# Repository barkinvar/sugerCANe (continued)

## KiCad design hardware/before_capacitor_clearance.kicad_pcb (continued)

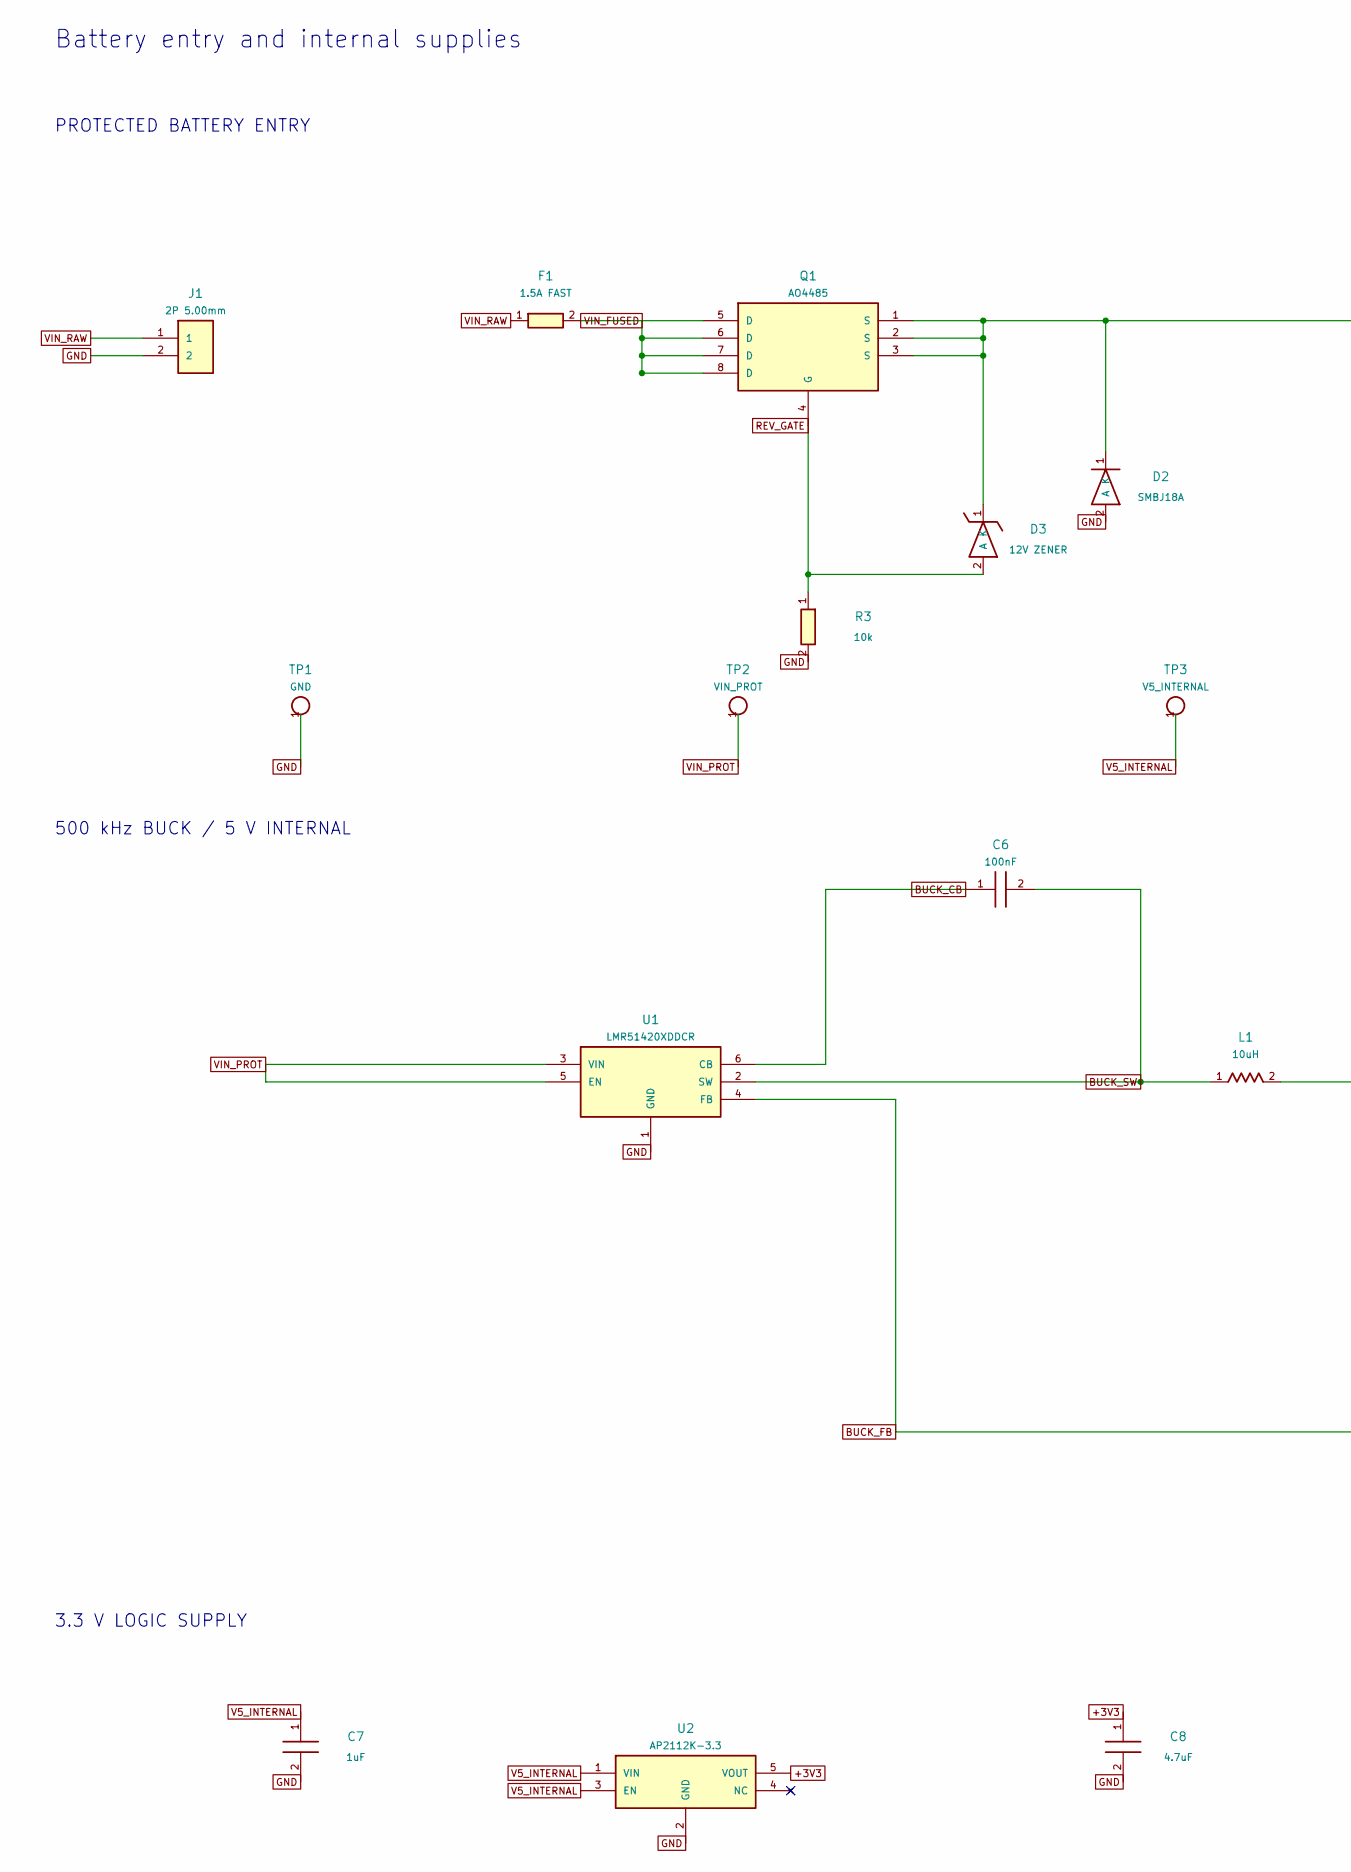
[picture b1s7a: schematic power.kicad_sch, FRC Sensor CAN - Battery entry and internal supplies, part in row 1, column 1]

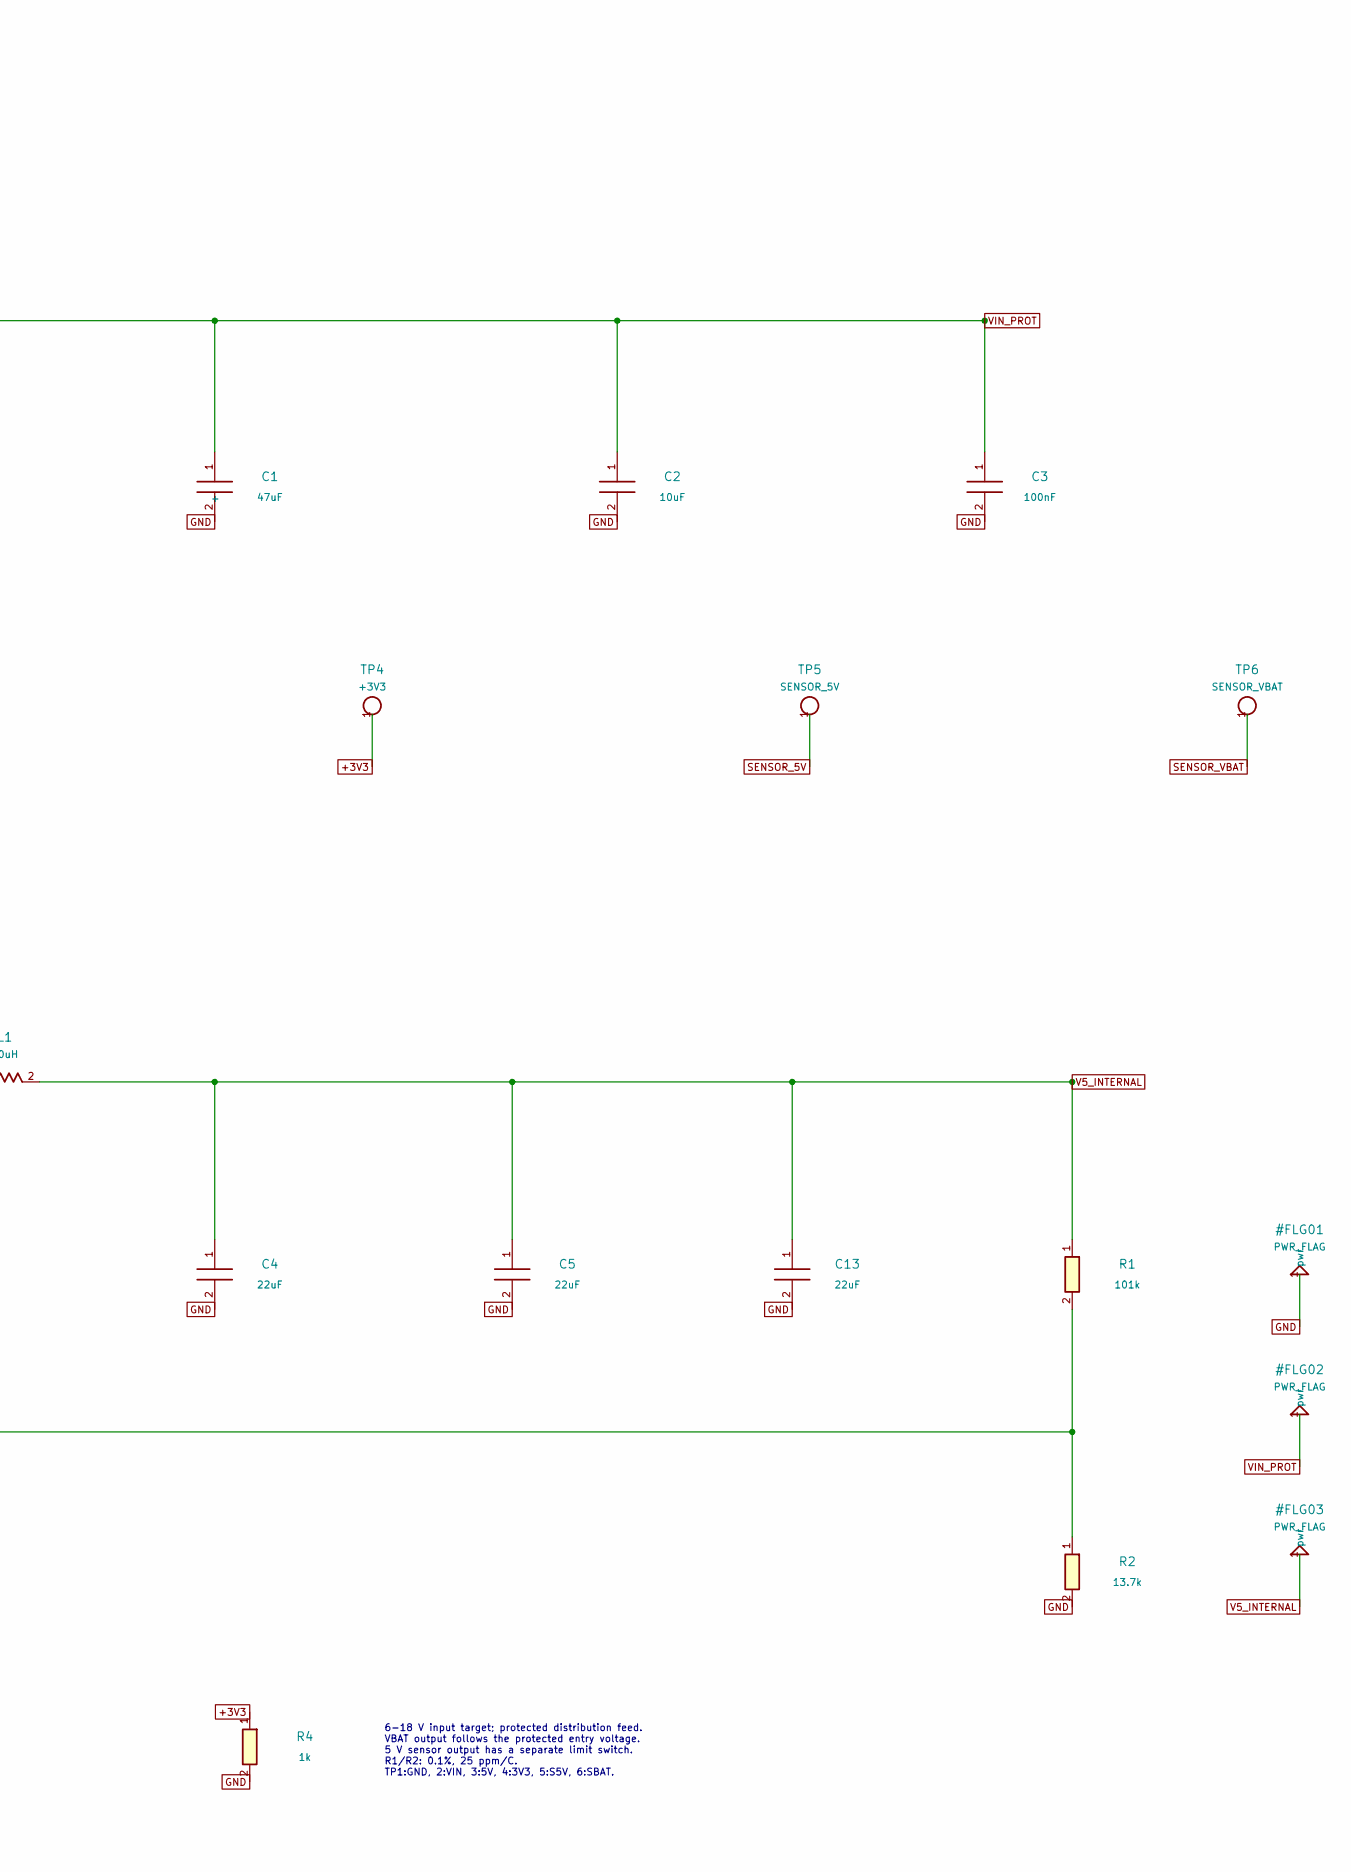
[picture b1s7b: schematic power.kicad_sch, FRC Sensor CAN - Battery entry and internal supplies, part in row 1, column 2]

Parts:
C1: 47uF; CP_Elec_6.3x5.8; MPN EEE-FK1V470P
C2: 10uF; C_1210_3225Metric; MPN CL32B106KBJNNWE
C3, C6: 100nF; C_0805_2012Metric; MPN CC0805KRX7R9BB104
C4, C5, C13: 22uF; C_1206_3216Metric; MPN CL31A226KAHNNNE
C7: 1uF; C_0805_2012Metric; MPN CC0805KKX7R9BB105
C8: 4.7uF; C_0805_2012Metric; MPN TMK212AB7475KG-T
D2: SMBJ18A; D_SMB; MPN SMBJ18A-E3/52
D3: 12V ZENER; D_SOD-123; MPN MMSZ12T1G
F1: 1.5A FAST; Fuse_Littelfuse-NANO2-451_453; MPN 045101.5MRL
J1: 2P 5.00mm; Wuerth_691137710002; MPN 691137710002
L1: 10uH; L_Bourns_SRP7028A_7.3x6.6mm; MPN SRP7028A-100M
Q1: AO4485; SOIC-8_3.9x4.9mm_P1.27mm; MPN AO4485
R1: 101k; R_0805_2012Metric; MPN RT0805BRD07101KL
R2: 13.7k; R_0805_2012Metric; MPN RT0805BRD0713K7L
R3: 10k; R_0805_2012Metric; MPN RC0805FR-0710KL
R4: 1k; R_0805_2012Metric; MPN RC0805FR-071KL
TP1: GND; TestPoint_Pad_D2.0mm
TP2: VIN_PROT; TestPoint_Pad_D2.0mm
TP3: V5_INTERNAL; TestPoint_Pad_D2.0mm
TP4: +3V3; TestPoint_Pad_D2.0mm
TP5: SENSOR_5V; TestPoint_Pad_D2.0mm
TP6: SENSOR_VBAT; TestPoint_Pad_D2.0mm
U1: LMR51420XDDCR; TSOT-23-6; MPN LMR51420XDDCR
U2: AP2112K-3.3; SOT-23-5; MPN AP2112K-3.3TRG1

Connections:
+3V3: C8.1, R4.1, TP4.1, U2.5 (VOUT); also elsewhere on the board
BUCK_CB: C6.1, U1.6 (CB)
BUCK_FB: R1.2, R2.1, U1.4 (FB)
BUCK_SW: C6.2, L1.1, U1.2 (SW)
GND: C1.2, C2.2, C3.2, C4.2, C5.2, C7.2, C8.2, C13.2, D2.2 (A), J1.2, R2.2, R3.2, R4.2, TP1.1, U1.1 (GND), U2.2 (GND); also elsewhere on the board
REV_GATE: D3.2 (A), Q1.4 (G), R3.1
SENSOR_5V: TP5.1; also elsewhere on the board
SENSOR_VBAT: TP6.1; also elsewhere on the board
V5_INTERNAL: C4.1, C5.1, C7.1, C13.1, L1.2, R1.1, TP3.1, U2.1 (VIN), U2.3 (EN); also elsewhere on the board
VIN_FUSED: F1.2, Q1.5 (D), Q1.6 (D), Q1.7 (D), Q1.8 (D)
VIN_PROT: C1.1 (+), C2.1, C3.1, D2.1 (K), D3.1 (K), Q1.1 (S), Q1.2 (S), Q1.3 (S), TP2.1, U1.3 (VIN), U1.5 (EN); also elsewhere on the board
VIN_RAW: F1.1, J1.1

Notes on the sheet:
Battery entry and internal supplies
PROTECTED BATTERY ENTRY
500 kHz BUCK / 5 V INTERNAL
3.3 V LOGIC SUPPLY
6-18 V input target; protected distribution feed. VBAT output follows the protected entry voltage. 5 V sensor output has a separate limit switch. R1/R2: 0.1%, 25 ppm/C. TP1:GND, 2:VIN, 3:5V, 4:3V3, 5:S5V, 6:SBAT.

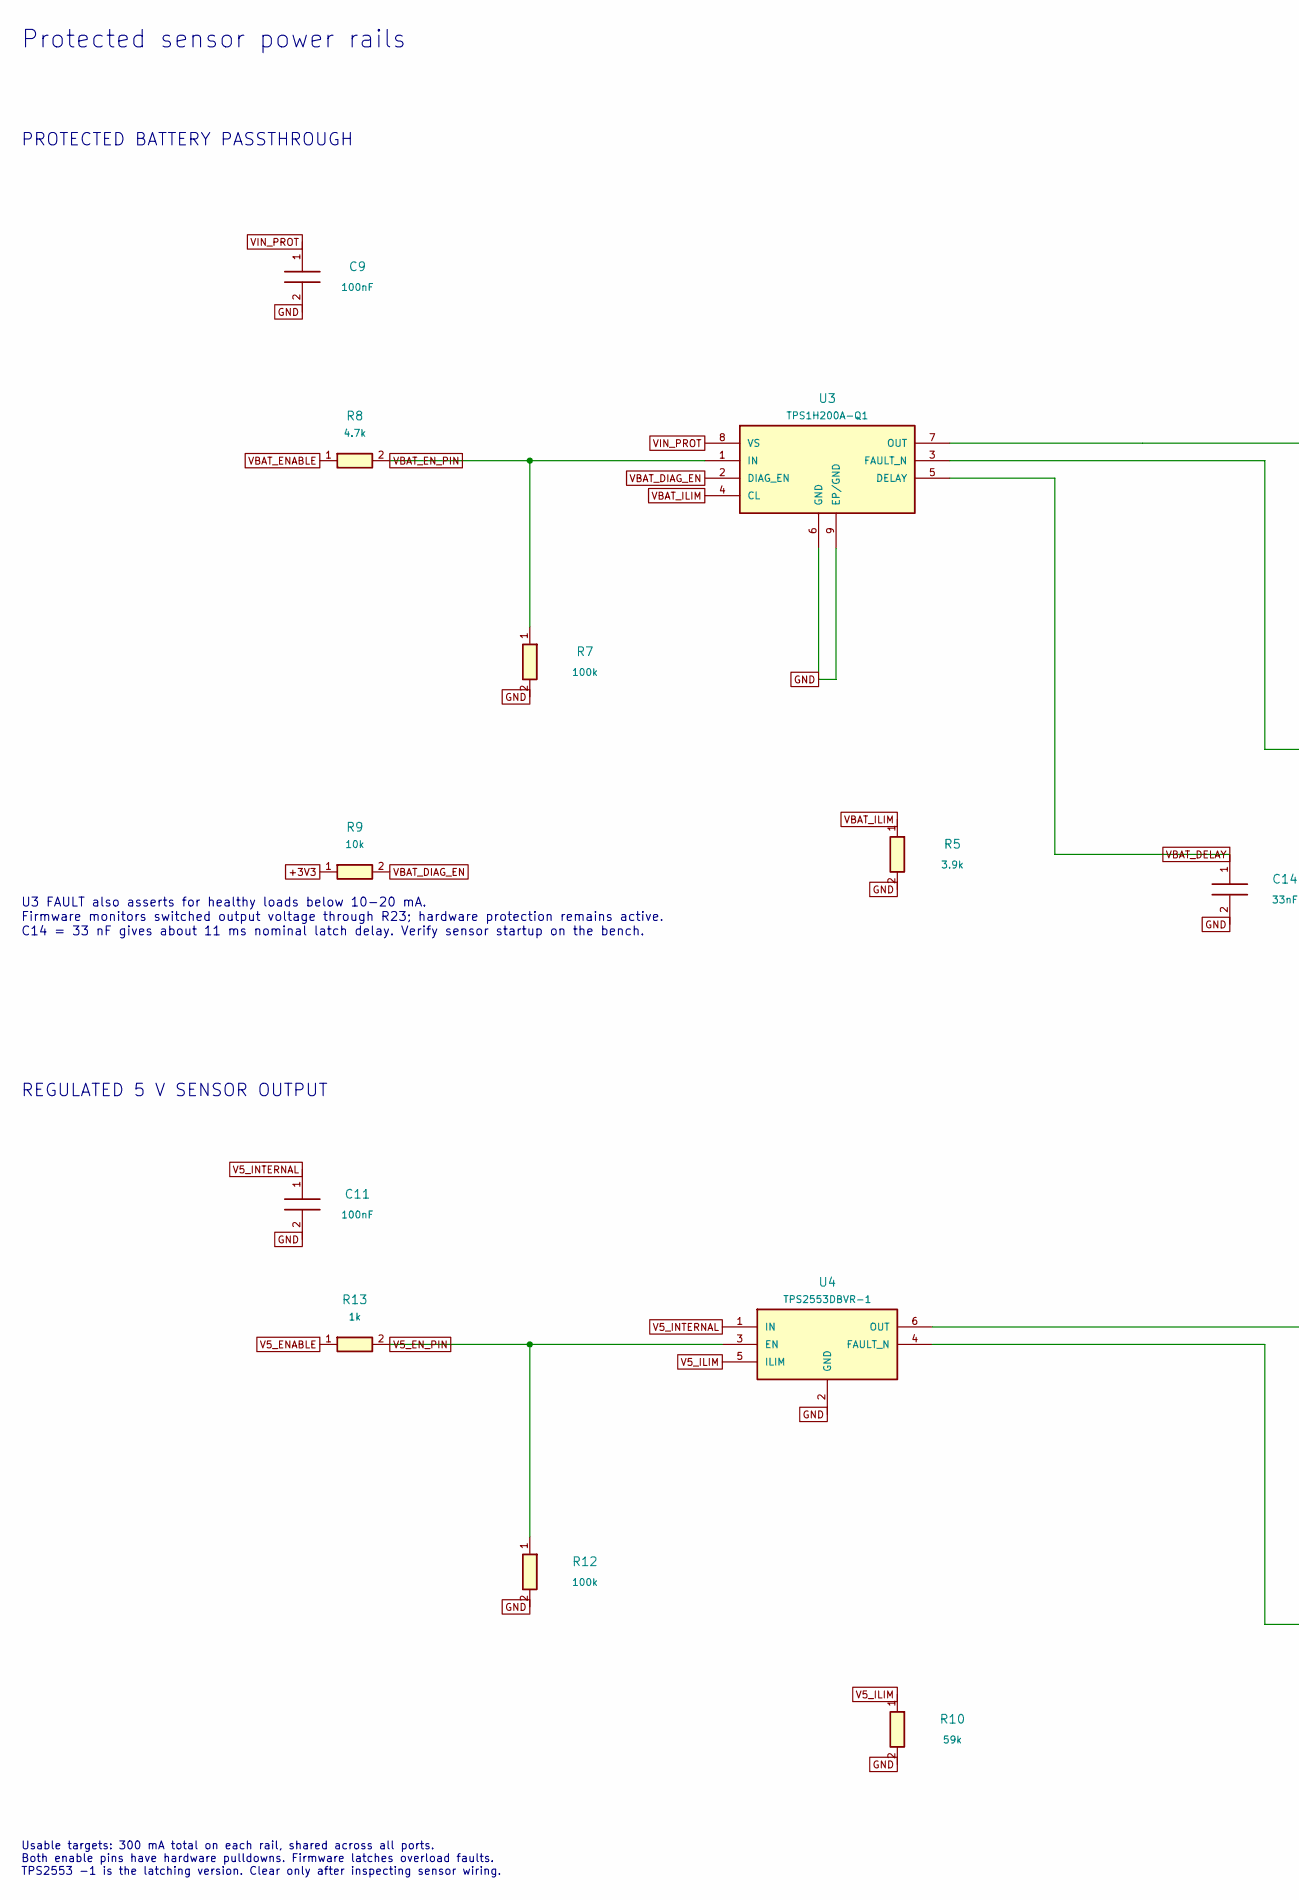
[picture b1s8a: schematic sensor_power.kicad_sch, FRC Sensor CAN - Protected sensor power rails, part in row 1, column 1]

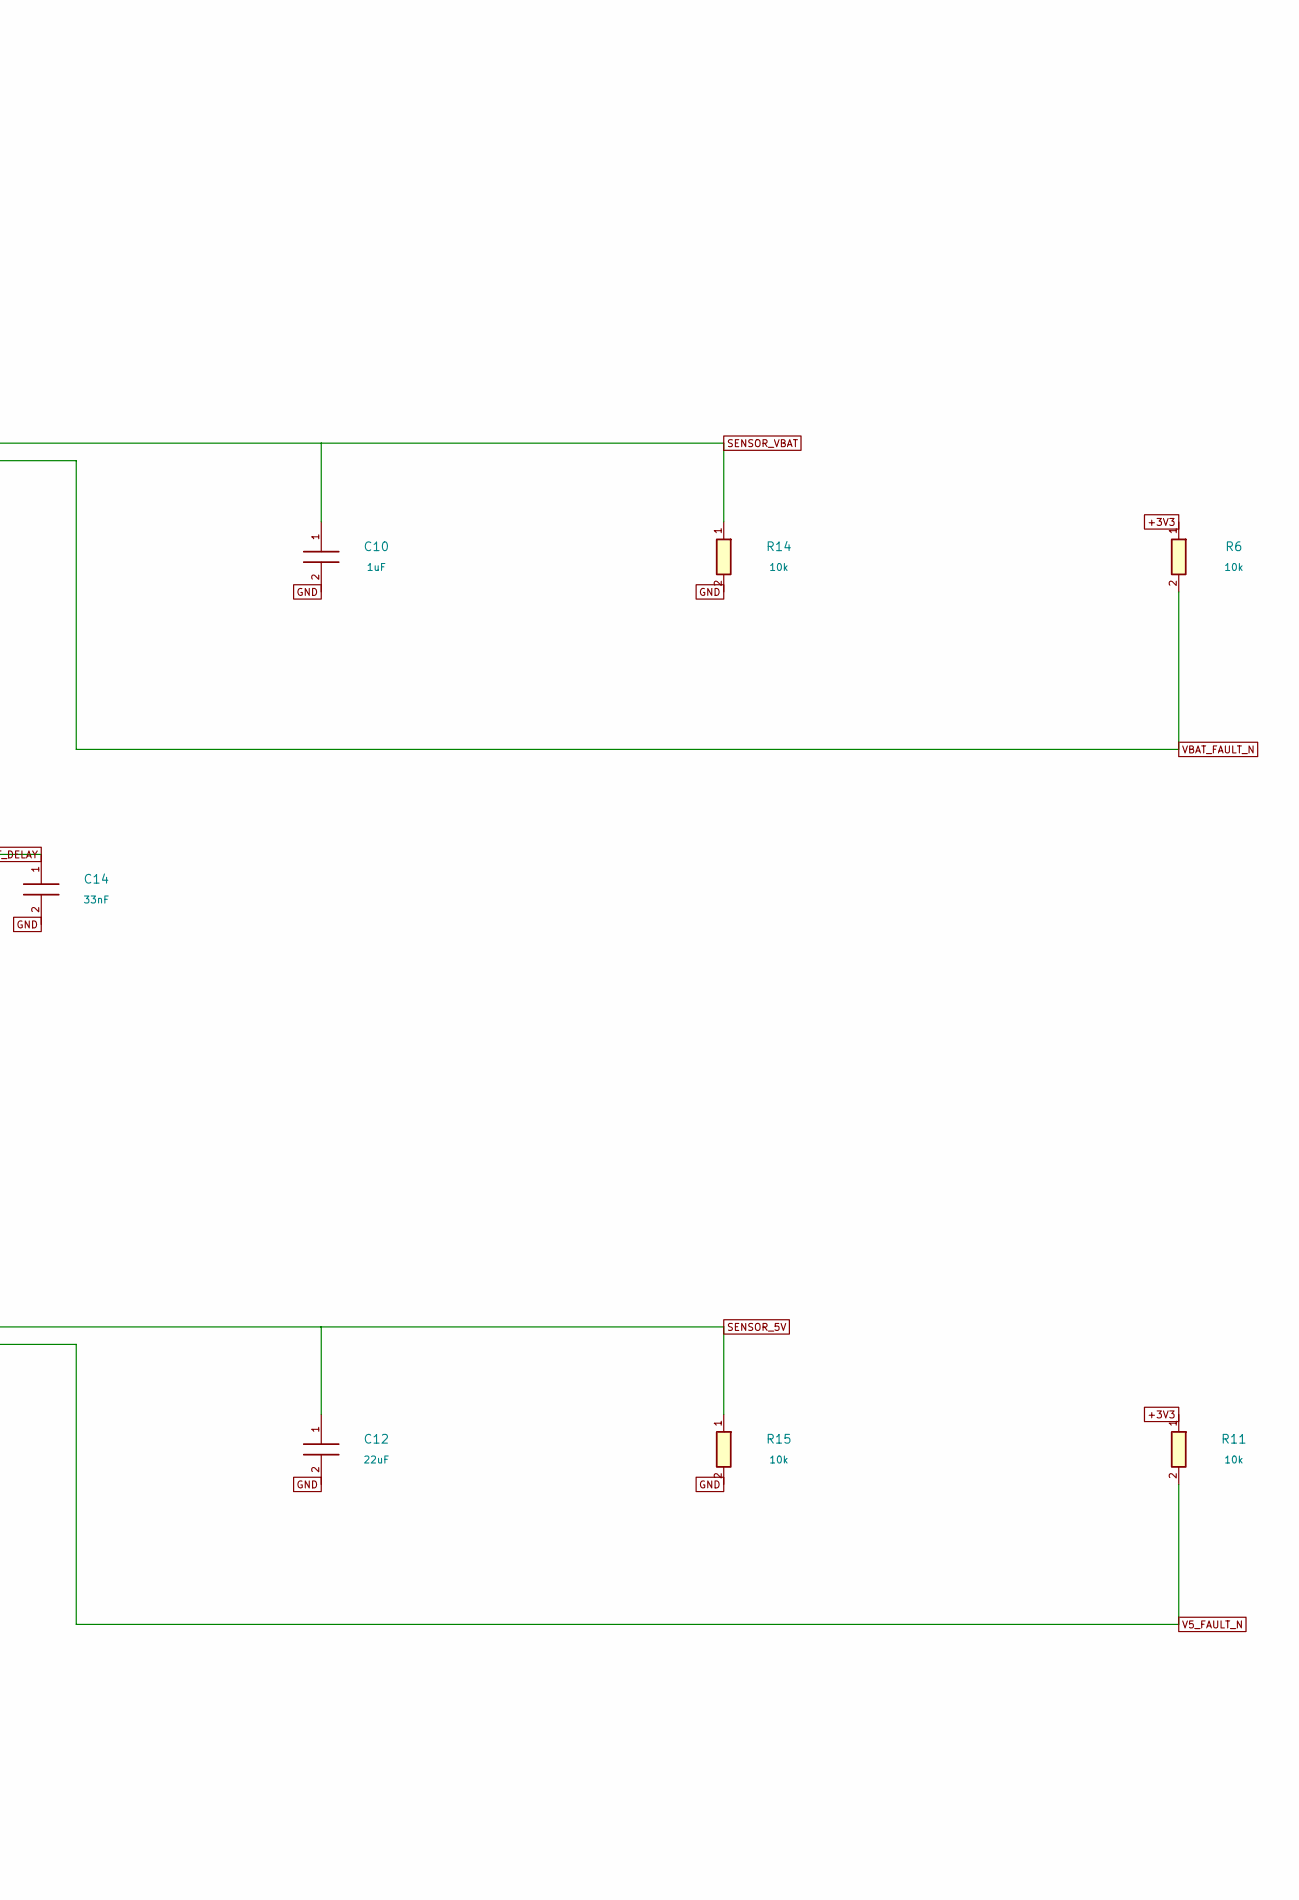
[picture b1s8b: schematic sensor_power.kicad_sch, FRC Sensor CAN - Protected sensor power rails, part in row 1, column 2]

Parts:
C9, C11: 100nF; C_0805_2012Metric; MPN CC0805KRX7R9BB104
C10: 1uF; C_0805_2012Metric; MPN CC0805KKX7R9BB105
C12: 22uF; C_1206_3216Metric; MPN CL31A226KAHNNNE
C14: 33nF; C_0805_2012Metric; MPN CC0805KRX7R9BB333
R5: 3.9k; R_0805_2012Metric; MPN RC0805FR-073K9L
R6, R9, R11, R14, R15: 10k; R_0805_2012Metric; MPN RC0805FR-0710KL
R7, R12: 100k; R_0805_2012Metric; MPN RC0805FR-07100KL
R8: 4.7k; R_0805_2012Metric; MPN RC0805FR-074K7L
R10: 59k; R_0805_2012Metric; MPN RC0805FR-0759KL
R13: 1k; R_0805_2012Metric; MPN RC0805FR-071KL
U3: TPS1H200A-Q1; TI_DGN0008K_HVSSOP8_EP; MPN TPS1H200AQDGNRQ1
U4: TPS2553DBVR-1; SOT-23-6; MPN TPS2553DBVR-1

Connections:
+3V3: R6.1, R9.1, R11.1; also elsewhere on the board
GND: C9.2, C10.2, C11.2, C12.2, C14.2, R5.2, R7.2, R10.2, R12.2, R14.2, R15.2, U3.6 (GND), U3.9 (EP/GND), U4.2 (GND); also elsewhere on the board
SENSOR_5V: C12.1, R15.1, U4.6 (OUT); also elsewhere on the board
SENSOR_VBAT: C10.1, R14.1, U3.7 (OUT); also elsewhere on the board
V5_ENABLE: R13.1; also elsewhere on the board
V5_EN_PIN: R12.1, R13.2, U4.3 (EN)
V5_FAULT_N: R11.2, U4.4 (FAULT_N); also elsewhere on the board
V5_ILIM: R10.1, U4.5 (ILIM)
V5_INTERNAL: C11.1, U4.1 (IN); also elsewhere on the board
VBAT_DELAY: C14.1, U3.5 (DELAY)
VBAT_DIAG_EN: R9.2, U3.2 (DIAG_EN)
VBAT_ENABLE: R8.1; also elsewhere on the board
VBAT_EN_PIN: R7.1, R8.2, U3.1 (IN)
VBAT_FAULT_N: R6.2, U3.3 (FAULT_N); also elsewhere on the board
VBAT_ILIM: R5.1, U3.4 (CL)
VIN_PROT: C9.1, U3.8 (VS); also elsewhere on the board

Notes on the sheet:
Protected sensor power rails
PROTECTED BATTERY PASSTHROUGH
U3 FAULT also asserts for healthy loads below 10-20 mA. Firmware monitors switched output voltage through R23; hardware protection remains active. C14 = 33 nF gives about 11 ms nominal latch delay. Verify sensor startup on the bench.
REGULATED 5 V SENSOR OUTPUT
Usable targets: 300 mA total on each rail, shared across all ports. Both enable pins have hardware pulldowns. Firmware latches overload faults. TPS2553 -1 is the latching version. Clear only after inspecting sensor wiring.

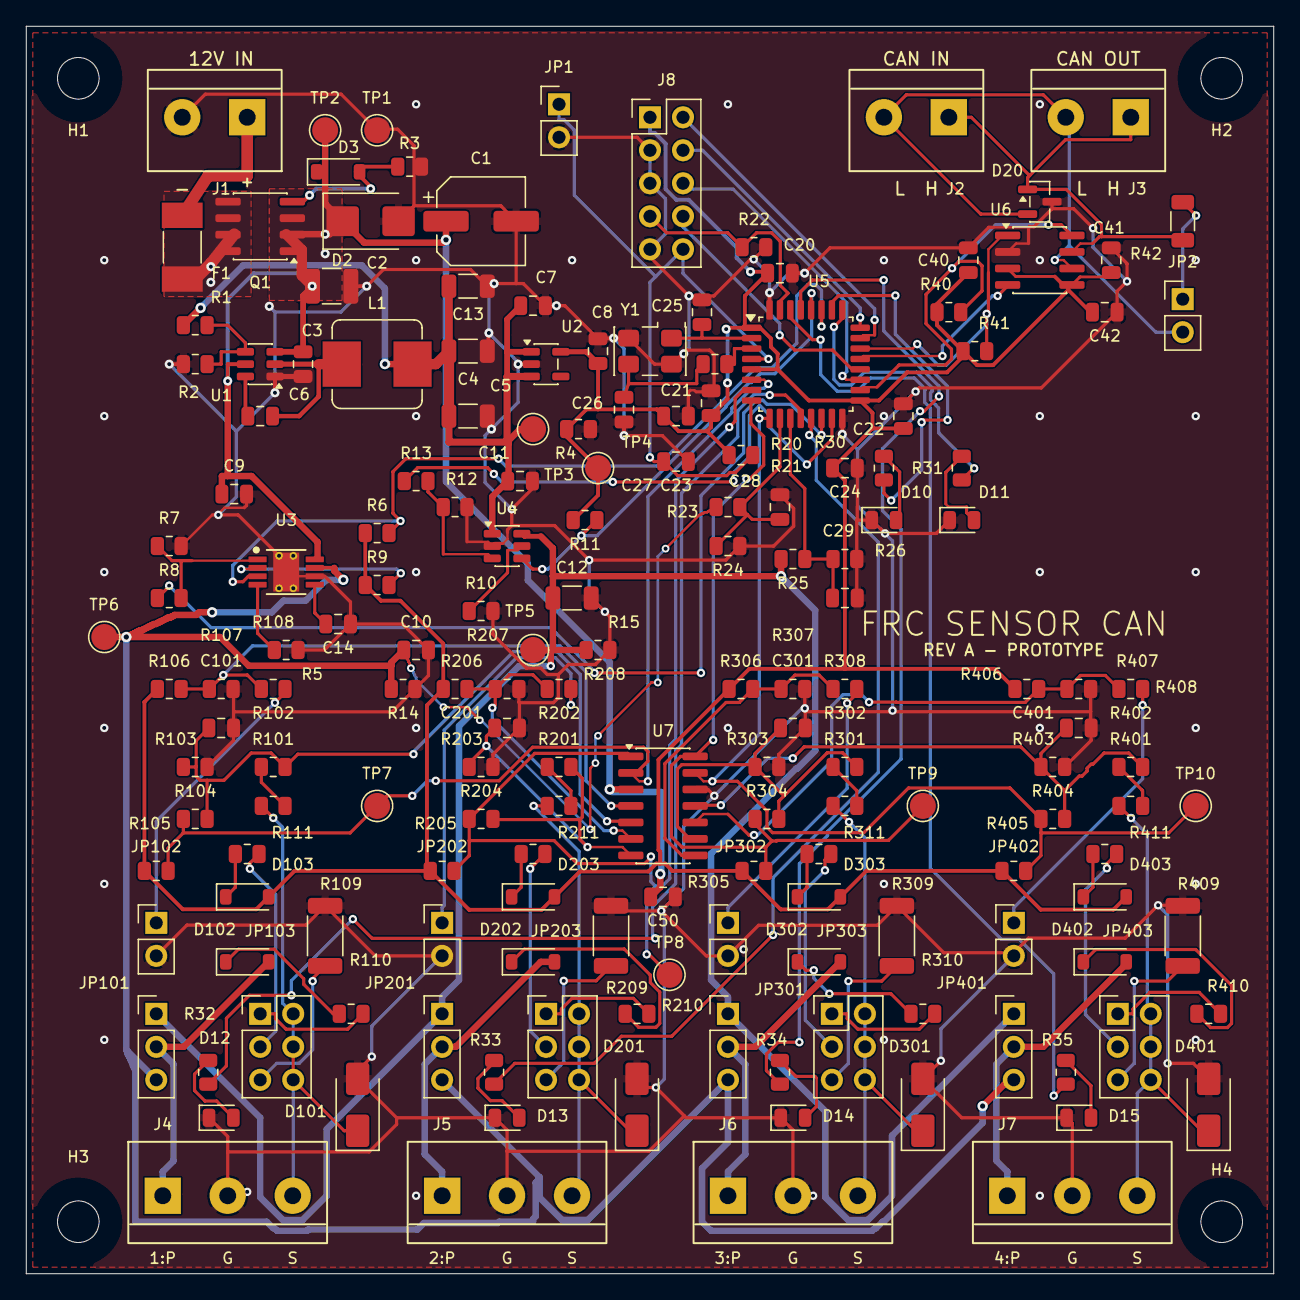
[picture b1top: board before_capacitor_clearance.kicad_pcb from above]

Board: 2 copper layers, 96.0 x 96.0 mm, 175 parts (0 on the bottom side), 99 nets.

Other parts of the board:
H1, H2, H3, H4: M3 NPTH

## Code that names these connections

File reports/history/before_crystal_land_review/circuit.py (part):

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# Two protected sensor power rails.
s='sensor_power'
component('U3','HSD','TPS1H200A-Q1',{
    1:'VBAT_EN_PIN',2:'VBAT_DIAG_EN',3:'VBAT_FAULT_N',4:'VBAT_ILIM',5:'VBAT_DELAY',
    6:'GND',7:'SENSOR_VBAT',8:'VIN_PROT',9:'GND'},s,
    'FRC_Sensor_CAN:TI_DGN0008K_HVSSOP8_EP',mpn='TPS1H200AQDGNRQ1')
resistor('R5','3.9k','VBAT_ILIM','GND',s,mpn='RC0805FR-073K9L')
cap('C14','33nF','VBAT_DELAY','GND',s,mpn='CC0805KRX7R9BB333',note='Hardware latch-off after ~11ms in current limit; allows sensor inrush; no automatic retry.')
resistor('R6','10k','+3V3','VBAT_FAULT_N',s)
resistor('R7','100k','VBAT_EN_PIN','GND',s)
resistor('R8','4.7k','VBAT_ENABLE','VBAT_EN_PIN',s)
resistor('R9','10k','+3V3','VBAT_DIAG_EN',s)
cap('C9','100nF','VIN_PROT','GND',s)
cap('C10','1uF','SENSOR_VBAT','GND',s)
component('U4','LOADSW','TPS2553DBVR-1',{1:'V5_INTERNAL',2:'GND',3:'V5_EN_PIN',4:'V5_FAULT_N',5:'V5_ILIM',6:'SENSOR_5V'},s,
          'Package_TO_SOT_SMD:SOT-23-6',mpn='TPS2553DBVR-1')
resistor('R10','59k','V5_ILIM','GND',s)
resistor('R11','10k','+3V3','V5_FAULT_N',s)
resistor('R12','100k','V5_EN_PIN','GND',s)
resistor('R13','1k','V5_ENABLE','V5_EN_PIN',s)
cap('C11','100nF','V5_INTERNAL','GND',s)
cap('C12','10uF','SENSOR_5V','GND',s,'1206','25V')
resistor('R14','10k','SENSOR_VBAT','GND',s,note='Discharges output and absorbs bias-diode leakage when off; 1.8mA at18V.')
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header('JP2',['CAN_TERM','CANL'],s,note='Optional 120-ohm termination: shipped OPEN.')

# Four identical independently selected channels. Comparator units split between sheets.
comp_pins={3:'VIN_PROT',12:'GND'}
for ch,(out,pplus,pminus) in enumerate([(2,5,4),(1,7,6),(14,9,8),(13,11,10)],1):
    s=f'input{ch}'
    prefix=ch*100
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    diode(f'D{prefix+1}','SMAJ30A','GND',sig,s,'SMA',mpn='SMAJ30A',note='30V working standoff; unidirectional transient clamp.')
    diode(f'D{prefix+2}','BAT46W',vp,f'BIAS_PORT{ch}',s,mpn='BAT46W-E3-18')
    diode(f'D{prefix+3}','BAT46W','+3V3',f'BIAS_3V3_{ch}',s,mpn='BAT46W-E3-18')
component('U7','COMP4','LM2901BIDR',comp_pins,'input1','Package_SO:SOIC-14_3.9x8.7mm_P1.27mm',mpn='LM2901BIDR')
cap('C50','100nF','VIN_PROT','GND','input1')

# Explicit test pads: no separate purchased part.
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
